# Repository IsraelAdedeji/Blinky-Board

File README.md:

# Blinky-Board
A custom PCB designed to blink LEDs at variable speeds and intervals
My first PCB. Its a butterfly, aint that cool?

# Image

# Schematic, Footprint Mapping and PCB Design Image

# Bill Of Materials
[Blinky Board-bom (2).csv](https://github.com/user-attachments/files/29165458/Blinky.Board-bom.2.csv)

| Name | Purpose | Quantity | Total Cost (USD) | Link | Distributor |
|---:|---|---|---|---|---:|
| Potentiometer | Gets range input | 1 | 0.00 | https://www.aliexpress.com/item/1005012093971113.html | Aliexpress |
| LEDs | Emitting Light With Current | 0 | 0.00 | https://www.aliexpress.com/item/1005008040796418.html | Aliexpress |
| Capacitors | Stores Electrical Energy | 2 | 0.00 | https://www.aliexpress.com/item/1005005558643765.html | Aliexpress |
| Controller IC (CD4017) | IC to control LEDS | 1 | 0.00 | https://www.aliexpress.com/item/1005010146574961.html | Aliexpress |
| Timer IC (NE555N) | Controls timing of led blinks | 1 | 0.00 | https://www.aliexpress.com/item/32821209180.html | Aliexpress |
| Resistors | Resists Current Flow | 3 | 0.00 | https://www.aliexpress.com/item/32847096736.html | Aliexpress |
| PCB | Its the PCB for the project | 1 | 2.00 | https://cart.jlcpcb.com | JLCPCB |

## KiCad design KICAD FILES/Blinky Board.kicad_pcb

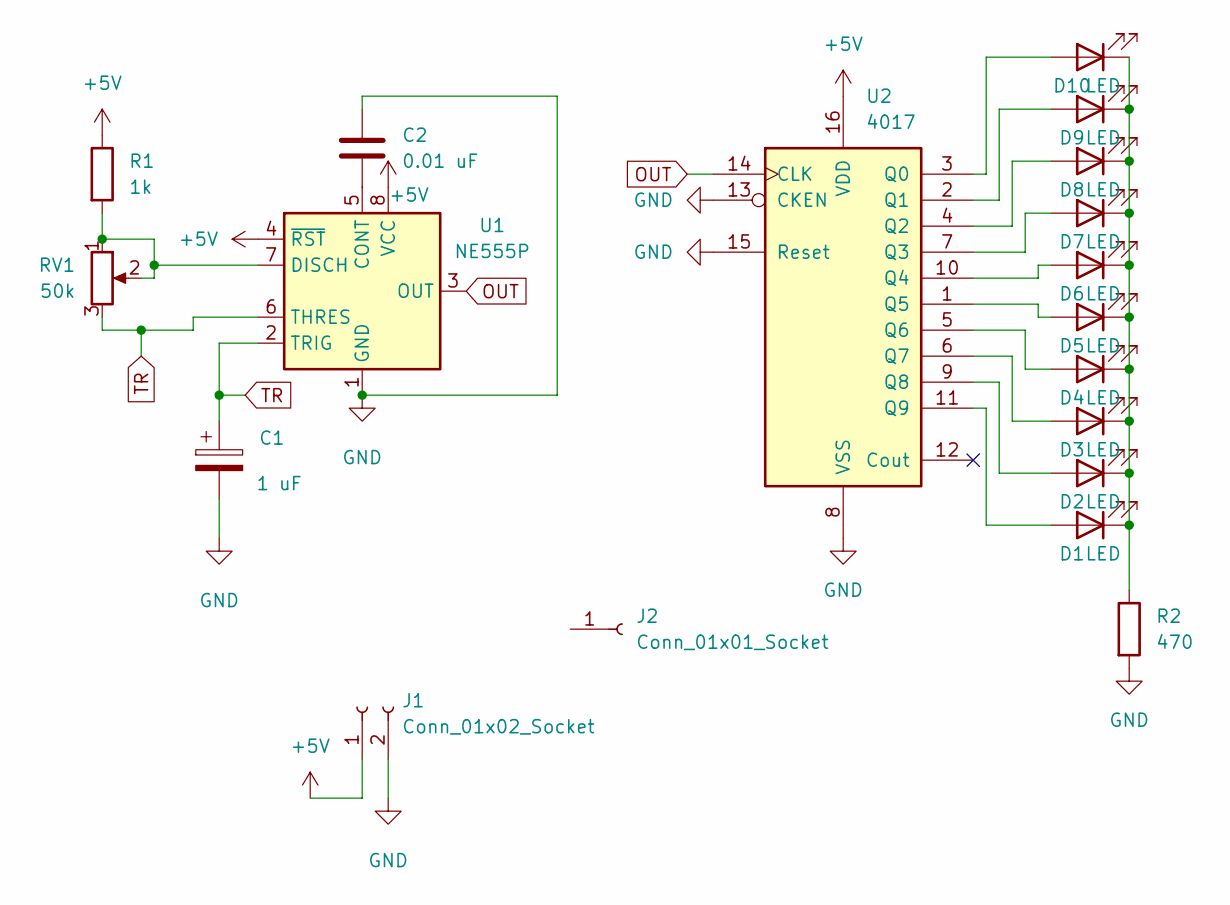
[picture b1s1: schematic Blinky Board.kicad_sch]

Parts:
C1: 1 uF; CP_Radial_D5.0mm_P2.00mm
C2: 0.01 uF; C_Disc_D7.5mm_W2.5mm_P5.00mm
D1, D2, D3, D4, D5, D6, D7, D8, D9, D10: LED; LED_D3.0mm
J1: Conn_01x02_Socket; PinHeader_1x02_P2.54mm_Vertical
J2: Conn_01x01_Socket; PinHeader_1x01_P2.54mm_Vertical
R1: 1k; R_Axial_DIN0207_L6.3mm_D2.5mm_P7.62mm_Horizontal
R2: 470; R_Axial_DIN0207_L6.3mm_D2.5mm_P7.62mm_Horizontal
RV1: 50k; Potentiometer_Vishay_T93YA_Vertical
U1: NE555P; DIP-8_W7.62mm
U2: 4017; N16

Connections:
+5V: J1.1, R1.1, U1.4 (~RST), U1.8 (VCC), U2.16 (VDD)
GND: C1.2, C2.2, J1.2, R2.2, U1.1 (GND), U2.8 (VSS), U2.13 (CKEN), U2.15 (Reset)
unnamed: D1.2 (A), U2.11 (Q9)
unnamed: D1.1 (K), D2.1 (K), D3.1 (K), D4.1 (K), D5.1 (K), D6.1 (K), D7.1 (K), D8.1 (K), D9.1 (K), D10.1 (K), R2.1
unnamed: D2.2 (A), U2.9 (Q8)
unnamed: D3.2 (A), U2.6 (Q7)
unnamed: D4.2 (A), U2.5 (Q6)
unnamed: D5.2 (A), U2.1 (Q5)
unnamed: D6.2 (A), U2.10 (Q4)
unnamed: D7.2 (A), U2.7 (Q3)
unnamed: D8.2 (A), U2.4 (Q2)
unnamed: D9.2 (A), U2.2 (Q1)
unnamed: D10.2 (A), U2.3 (Q0)
unnamed: C2.1, U1.5 (CONT)
unnamed: R1.2, RV1.1, RV1.2, U1.7 (DISCH)
OUT: U1.3 (OUT), U2.14 (CLK)
TR: C1.1, RV1.3, U1.2 (TRIG), U1.6 (THRES)

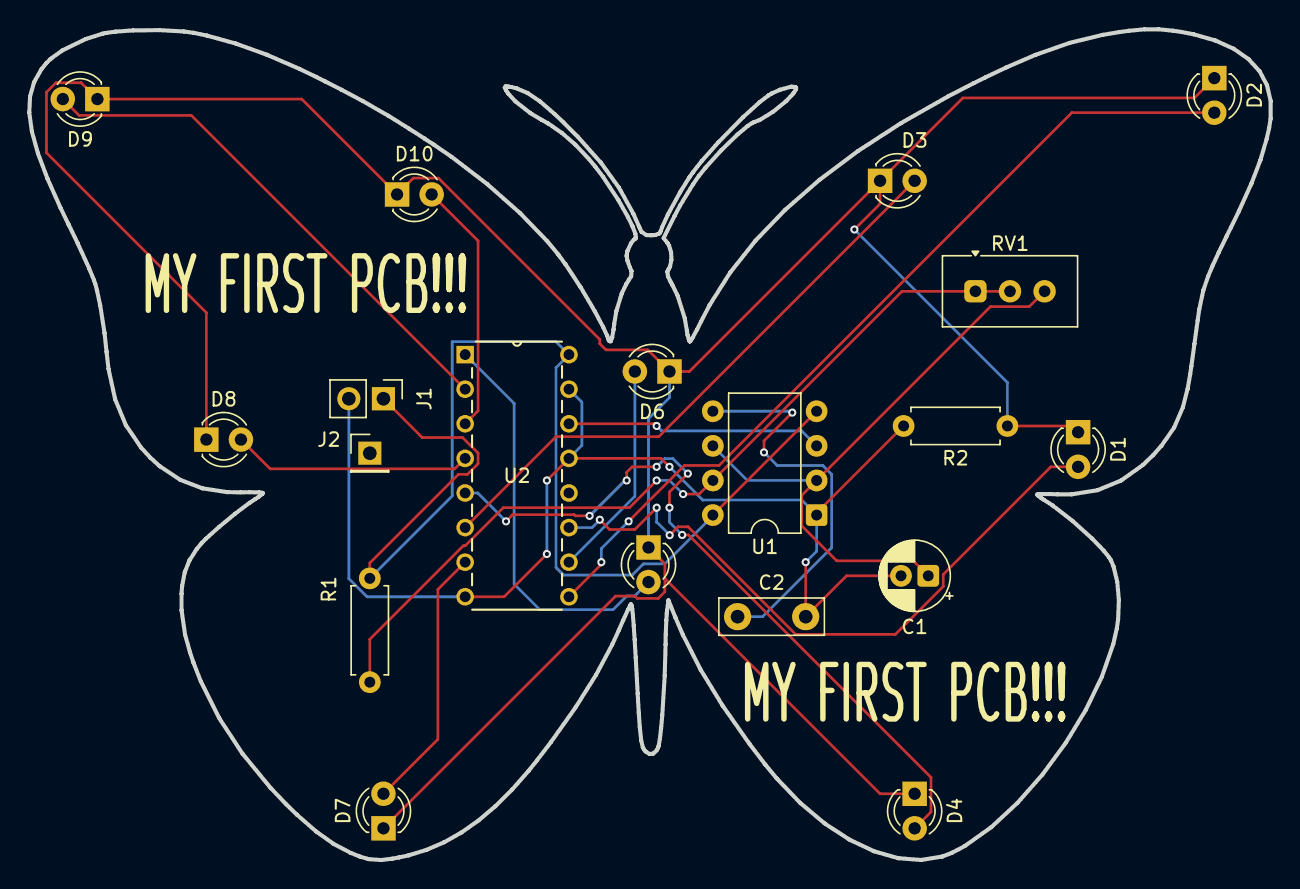
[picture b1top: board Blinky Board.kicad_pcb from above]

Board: 2 copper layers, 91.1 x 61.0 mm, 19 parts (0 on the bottom side), 17 nets.

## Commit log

2026-06-18 Create F
2026-06-18 Fix BOM.csv formatting and update PCB entry
2026-06-19 Update and rename KICAD FILES/F to KICAD FILES/EXTRAS/Footprint Mapping
2026-06-19 Revise Bill of Materials in README.md
    Updated the Bill of Materials with new components and links.
